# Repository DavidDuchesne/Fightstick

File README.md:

# Fightstick
Projet de fightstick avec stick analogique

Le débouncing est fait avec un filtre RC.

Fait avec le désign minimal pour le RP2040 fournie.

Gaming

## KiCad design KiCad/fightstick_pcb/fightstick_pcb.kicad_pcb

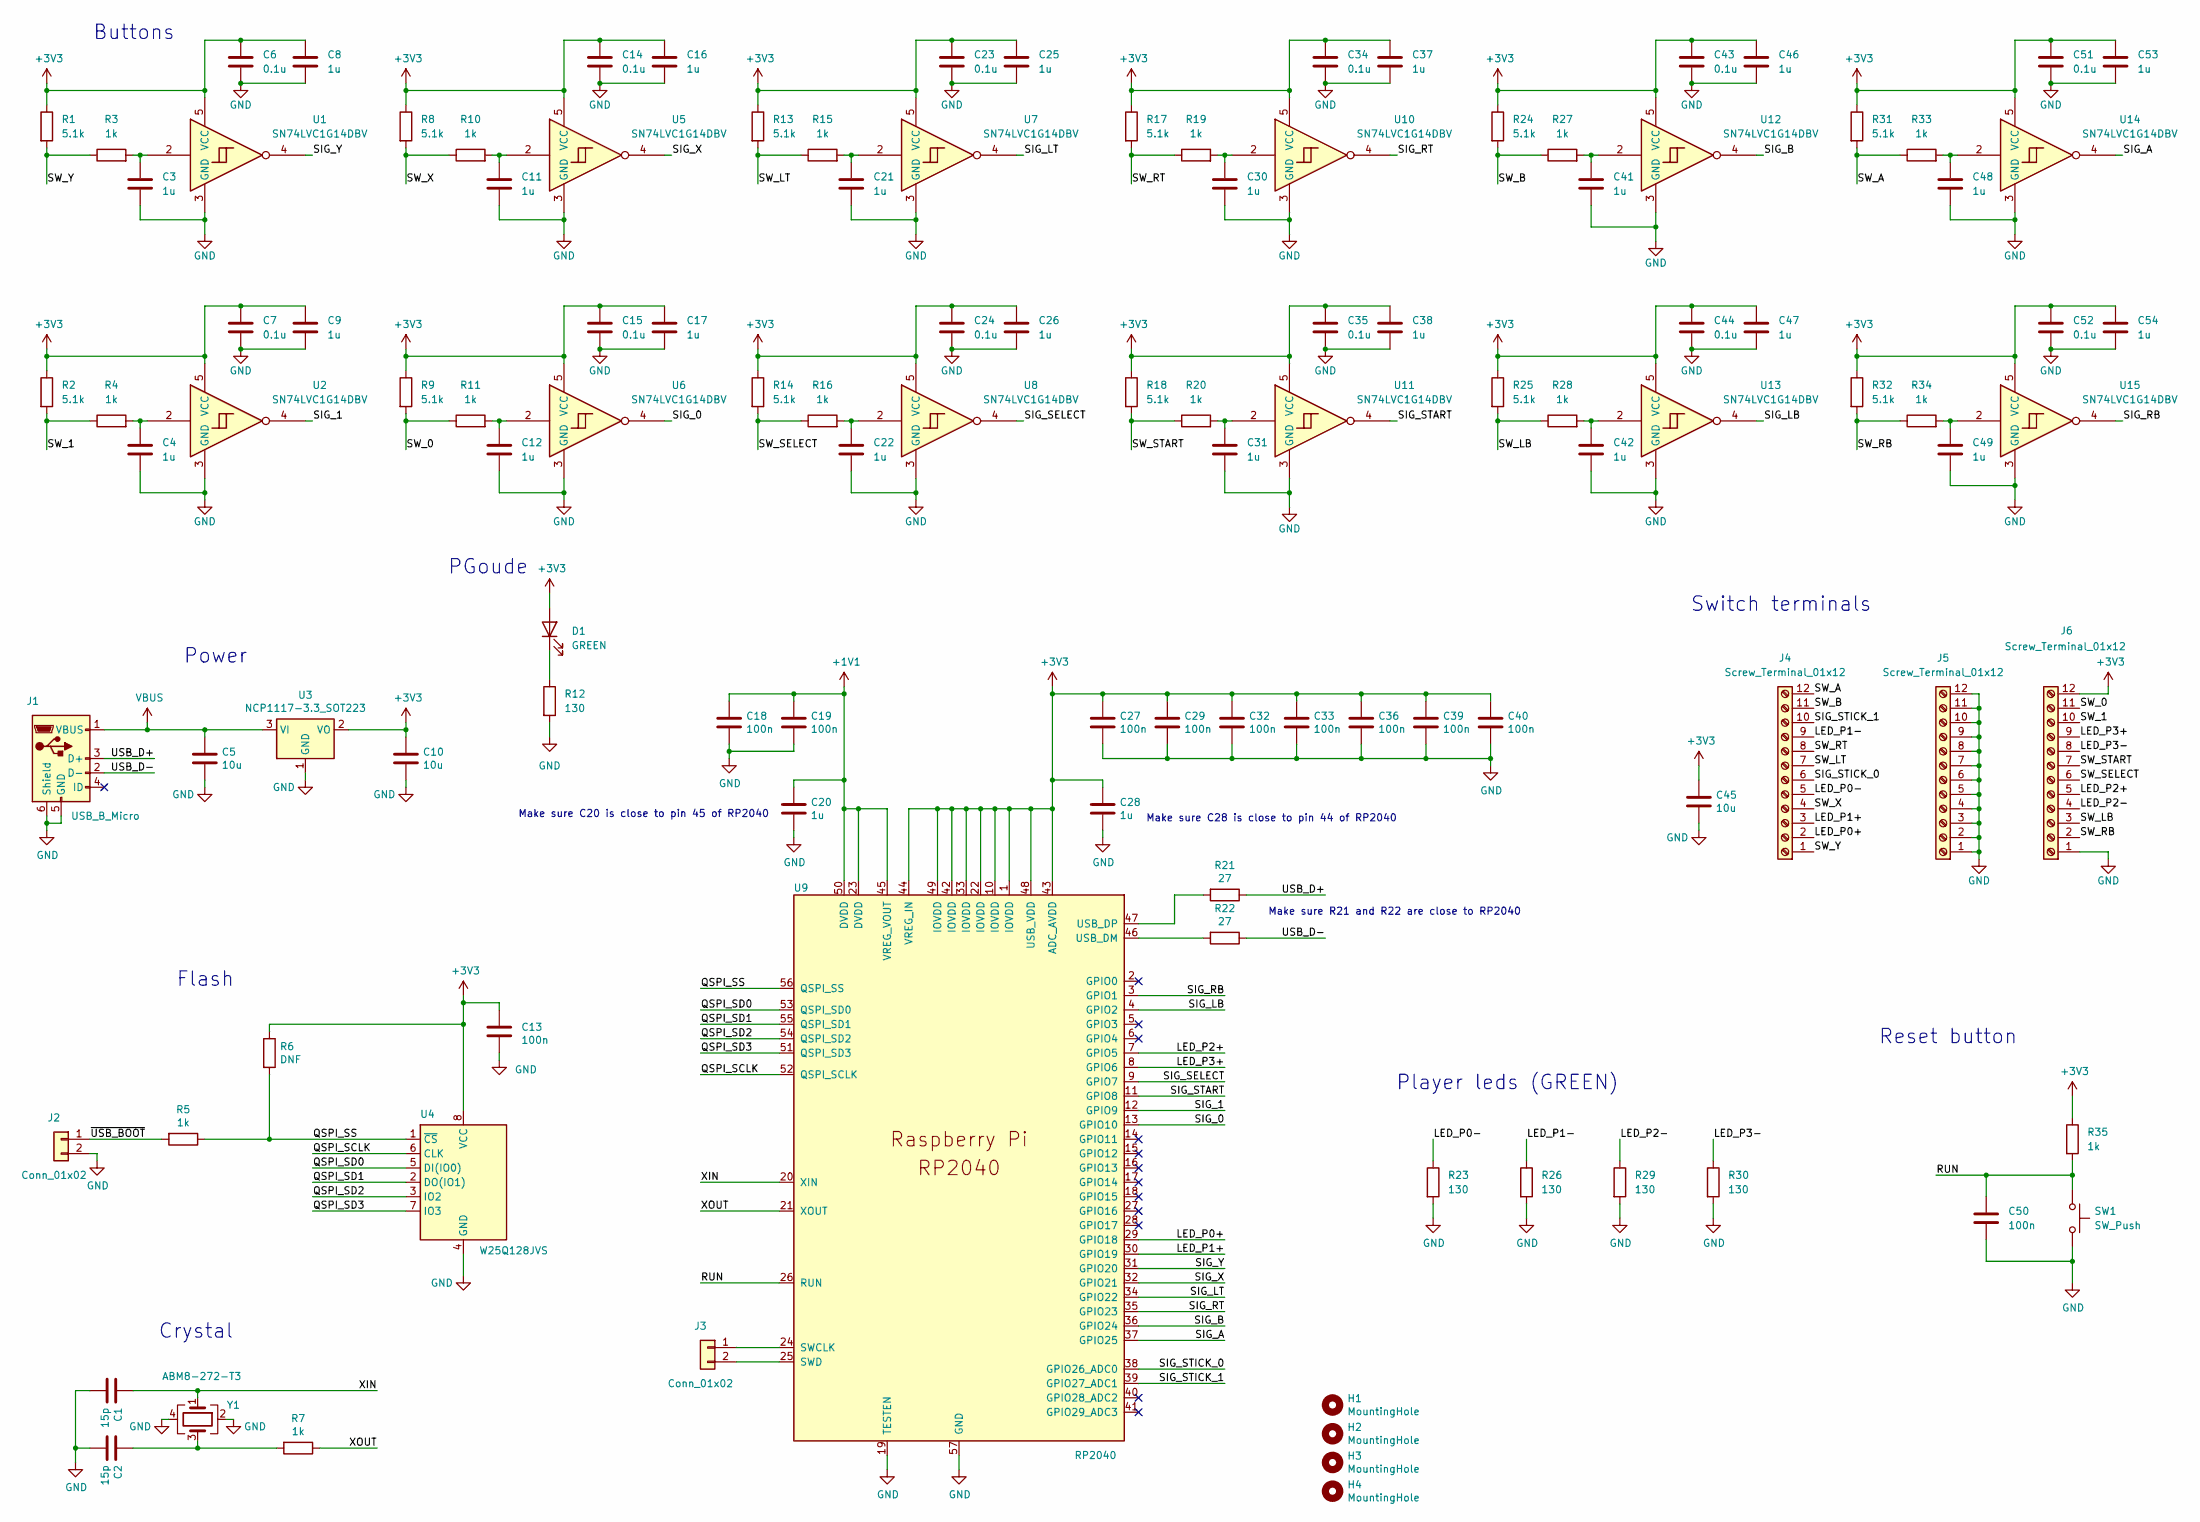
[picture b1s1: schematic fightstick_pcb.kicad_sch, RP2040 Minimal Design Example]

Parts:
C1, C2: 15p; C_0805_2012Metric
C3, C4, C8, C9, C11, C12, C16, C17, C20, C21, C22, C25, C26, C28, C30, C31, C37, C38, C41, C42, C46, C47, C48, C49, C53, C54: 1u; C_0805_2012Metric
C5, C10, C45: 10u; C_0805_2012Metric
C6, C7, C14, C15, C23, C24, C34, C35, C43, C44, C51, C52: 0.1u; C_0805_2012Metric
C13, C18, C19, C27, C29, C32, C33, C36, C39, C40, C50: 100n; C_0805_2012Metric
D1: GREEN; LED_0805_2012Metric
H1, H2, H3, H4: MountingHole; MountingHole_2.7mm_M2.5
J1: USB_B_Micro; USB_Micro-B_Amphenol_10103594-0001LF_Horizontal_modified
J2, J3: Conn_01x02; PinHeader_1x02_P2.54mm_Vertical
J4, J5, J6: Screw_Terminal_01x12; TerminalBlock_4Ucon_1x12_P3.50mm_Horizontal
R1, R2, R8, R9, R13, R14, R17, R18, R24, R25, R31, R32: 5.1k; R_0805_2012Metric
R3, R4, R5, R7, R10, R11, R15, R16, R19, R20, R27, R28, R33, R34, R35: 1k; R_0805_2012Metric
R6: DNF; R_0805_2012Metric
R12, R23, R26, R29, R30: 130; R_0805_2012Metric
R21, R22: 27; R_0805_2012Metric
SW1: SW_Push; SW_Push_1P1T_NO_6x6mm_H9.5mm
U1, U2, U5, U6, U7, U8, U10, U11, U12, U13, U14, U15: SN74LVC1G14DBV; SOT-23-5
U3: NCP1117-3.3_SOT223; SOT-223-3_TabPin2
U4: W25Q128JVS; SOIC-8_5.23x5.23mm_P1.27mm
U9: RP2040; RP2040-QFN-56
Y1: ABM8-272-T3; Crystal_SMD_3225-4Pin_3.2x2.5mm

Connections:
+1V1: C18.1, C19.1, C20.1, U9.23 (DVDD), U9.45 (VREG_VOUT), U9.50 (DVDD)
+3V3: C6.1, C7.1, C8.1, C9.1, C10.1, C13.1, C14.1, C15.1, C16.1, C17.1, C23.1, C24.1, C25.1, C26.1, C27.1, C28.1, C29.1, C32.1, C33.1, C34.1, C35.1, C36.1, C37.1, C38.1, C39.1, C40.1, C43.1, C44.1, C45.1, C46.1, C47.1, C51.1, C52.1, C53.1, C54.1, D1.2 (A), J6.12, R1.1, R2.1, R6.1, R8.1, R9.1, R13.1, R14.1, R17.1, R18.1, R24.1, R25.1, R31.1, R32.1, R35.1, U1.5 (VCC), U2.5 (VCC), U3.2 (VO), U4.8 (VCC), U5.5 (VCC), U6.5 (VCC), U7.5 (VCC), U8.5 (VCC), U9.1 (IOVDD), U9.10 (IOVDD), U9.22 (IOVDD), U9.33 (IOVDD), U9.42 (IOVDD), U9.43 (ADC_AVDD), U9.44 (VREG_IN), U9.48 (USB_VDD), U9.49 (IOVDD), U10.5 (VCC), U11.5 (VCC), U12.5 (VCC), U13.5 (VCC), U14.5 (VCC), U15.5 (VCC)
/LED_P0+: J4.2, U9.29 (GPIO18)
/LED_P0-: J4.5, R23.1
/LED_P1+: J4.3, U9.30 (GPIO19)
/LED_P1-: J4.9, R26.1
/LED_P2+: J6.5, U9.7 (GPIO5)
/LED_P2-: J6.4, R29.1
/LED_P3+: J6.9, U9.8 (GPIO6)
/LED_P3-: J6.8, R30.1
/QSPI_SCLK: U4.6 (CLK), U9.52 (QSPI_SCLK)
/QSPI_SD0: U4.5 (DI(IO0)), U9.53 (QSPI_SD0)
/QSPI_SD1: U4.2 (DO(IO1)), U9.55 (QSPI_SD1)
/QSPI_SD2: U4.3 (IO2), U9.54 (QSPI_SD2)
/QSPI_SD3: U4.7 (IO3), U9.51 (QSPI_SD3)
/QSPI_SS: R5.1, R6.2, U4.1 (~CS), U9.56 (QSPI_SS)
/RUN: C50.1, R35.2, SW1.1, U9.26 (RUN)
/SIG_0: U6.4, U9.13 (GPIO10)
/SIG_1: U2.4, U9.12 (GPIO9)
/SIG_A: U9.37 (GPIO25), U14.4
/SIG_B: U9.36 (GPIO24), U12.4
/SIG_LB: U9.4 (GPIO2), U13.4
/SIG_LT: U7.4, U9.34 (GPIO22)
/SIG_RB: U9.3 (GPIO1), U15.4
/SIG_RT: U9.35 (GPIO23), U10.4
/SIG_SELECT: U8.4, U9.9 (GPIO7)
/SIG_START: U9.11 (GPIO8), U11.4
/SIG_STICK_0: J4.6, U9.38 (GPIO26_ADC0)
/SIG_STICK_1: J4.10, U9.39 (GPIO27_ADC1)
/SIG_X: U5.4, U9.32 (GPIO21)
/SIG_Y: U1.4, U9.31 (GPIO20)
/SW_0: J6.11, R9.2, R11.1
/SW_1: J6.10, R2.2, R4.1
/SW_A: J4.12, R31.2, R33.1
/SW_B: J4.11, R24.2, R27.1
/SW_LB: J6.3, R25.2, R28.1
/SW_LT: J4.7, R13.2, R15.1
/SW_RB: J6.2, R32.2, R34.1
/SW_RT: J4.8, R17.2, R19.1
/SW_SELECT: J6.6, R14.2, R16.1
/SW_START: J6.7, R18.2, R20.1
/SW_X: J4.4, R8.2, R10.1
/SW_Y: J4.1, R1.2, R3.1
/USB_D+: J1.3 (D+), R21.1
/USB_D-: J1.2 (D-), R22.1
/XIN: C1.1, U9.20 (XIN), Y1.1
/XOUT: R7.1, U9.21 (XOUT)
/~USB_BOOT: J2.1, R5.2
GND: C1.2, C2.2, C3.2, C4.2, C5.2, C6.2, C7.2, C8.2, C9.2, C10.2, C11.2, C12.2, C13.2, C14.2, C15.2, C16.2, C17.2, C18.2, C19.2, C20.2, C21.2, C22.2, C23.2, C24.2, C25.2, C26.2, C27.2, C28.2, C29.2, C30.2, C31.2, C32.2, C33.2, C34.2, C35.2, C36.2, C37.2, C38.2, C39.2, C40.2, C41.2, C42.2, C43.2, C44.2, C45.2, C46.2, C47.2, C48.2, C49.2, C50.2, C51.2, C52.2, C53.2, C54.2, J1.5 (GND), J1.6 (Shield), J2.2, J5.1, J5.2, J5.3, J5.4, J5.5, J5.6, J5.7, J5.8, J5.9, J5.10, J5.11, J5.12, J6.1, R12.2, R23.2, R26.2, R29.2, R30.2, SW1.2, U1.3 (GND), U2.3 (GND), U3.1 (GND), U4.4 (GND), U5.3 (GND), U6.3 (GND), U7.3 (GND), U8.3 (GND), U9.19 (TESTEN), U9.57 (GND), U10.3 (GND), U11.3 (GND), U12.3 (GND), U13.3 (GND), U14.3 (GND), U15.3 (GND), Y1.2, Y1.4
unnamed: C2.1, R7.2, Y1.3
unnamed: C3.1, R3.2, U1.2
unnamed: C4.1, R4.2, U2.2
unnamed: C11.1, R10.2, U5.2
unnamed: C12.1, R11.2, U6.2
unnamed: C21.1, R15.2, U7.2
unnamed: C22.1, R16.2, U8.2
unnamed: C30.1, R19.2, U10.2
unnamed: C31.1, R20.2, U11.2
unnamed: C41.1, R27.2, U12.2
unnamed: C42.1, R28.2, U13.2
unnamed: C48.1, R33.2, U14.2
unnamed: C49.1, R34.2, U15.2
unnamed: D1.1 (K), R12.1
unnamed: J3.1, U9.24 (SWCLK)
unnamed: J3.2, U9.25 (SWD)
unnamed: R22.2, U9.46 (USB_DM)
unnamed: R21.2, U9.47 (USB_DP)
VBUS: C5.1, J1.1 (VBUS), U3.3 (VI)

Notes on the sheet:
Power
Crystal
Reset button
Make sure C20 is close to pin 45 of RP2040
Player leds (GREEN)
Switch terminals
Make sure C28 is close to pin 44 of RP2040
Buttons
Make sure R21 and R22 are close to RP2040
Flash
PGoude

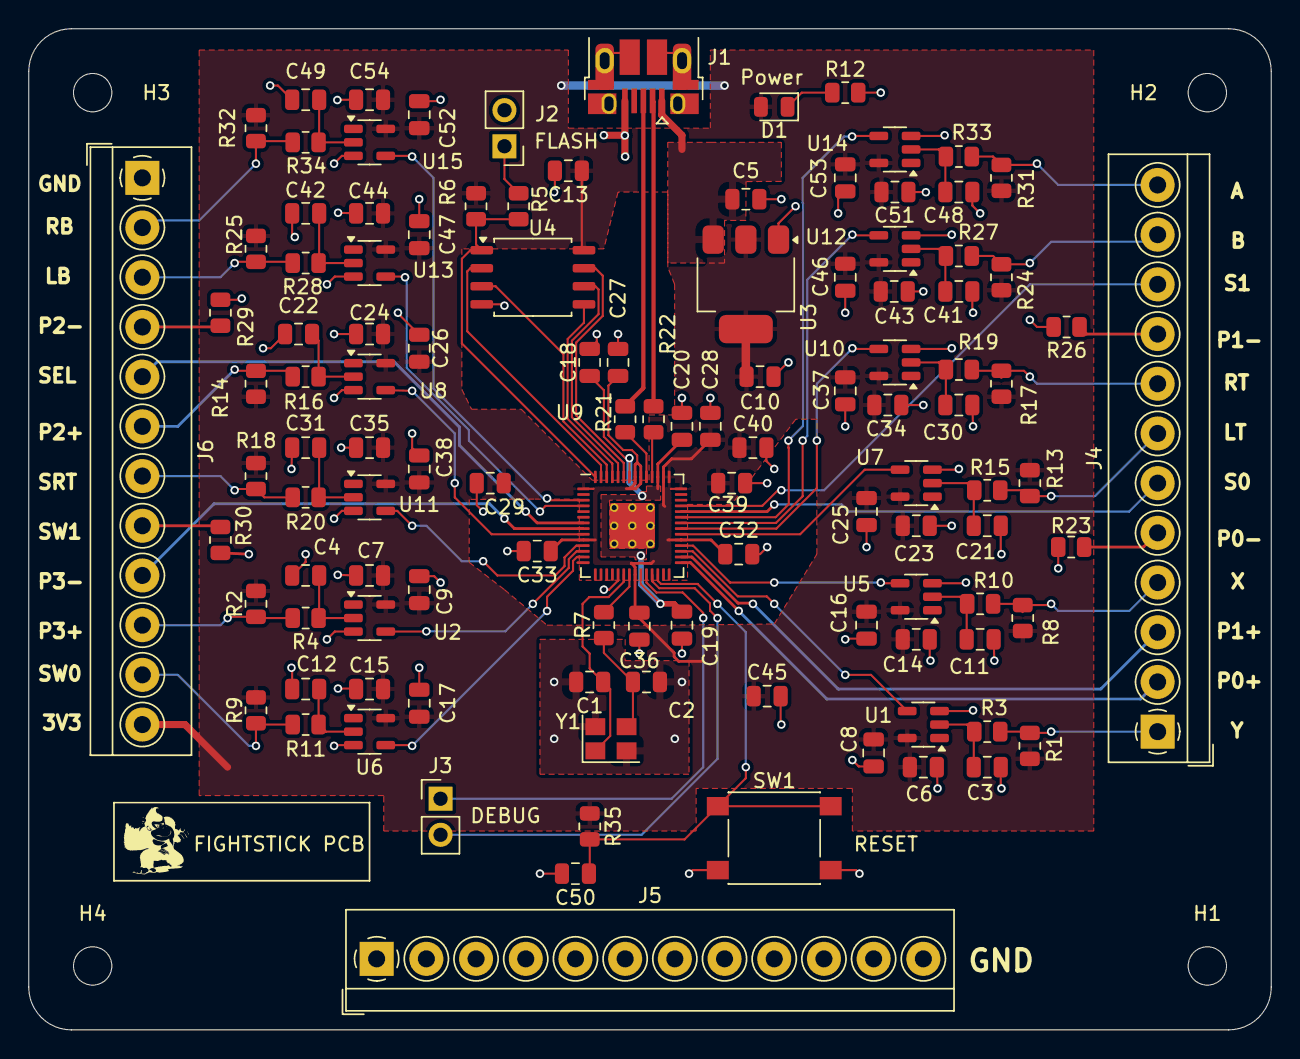
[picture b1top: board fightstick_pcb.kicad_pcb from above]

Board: 2 copper layers, 87.5 x 70.5 mm, 117 parts (0 on the bottom side), 68 nets.

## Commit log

2024-06-06 First draft
    Ajouté les pins pour le stick et les boutons.
2024-06-06 Added LEDs and Reset
    Added player leds, reset button and meaningfull pin names
2024-06-07 Added connectors
2024-06-11 Updated power symbols
2024-06-13 New terminals
2024-06-26 Recreation of minimal design
2024-06-26 Les circuits de debounce sont settés
2024-07-12 PCB Fightstick V1
2024-07-15 PCB V1.1.0
    Améliorations avec cap polarisés
2024-07-16 PCB V1.2
    Il n'y a plus de condensateurs polarisés
2024-07-16 PCB V1.2.1
    Tous les condensateurs et résistances sont maintenant plus gros
2024-07-30 Trace GND du USB agrandie
